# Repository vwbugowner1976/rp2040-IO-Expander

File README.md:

# RP2040-Zero BLE I/O Rev.W

Fresh mechanical-master revision for the RP2040-Zero BLE adapter concept.

- 18 × 23.5 mm
- RP2040-Zero THT/castellation geometry from the supplied master footprint
- USB-C + BOOT + RESET on F.Cu side
- 24P FFC on B.Cu side
- MDBT50Q-1MV2 is a separate core board
- FFC 1–20 = GPIO0–15, GPIO26–29
- FFC 21 = 3V3
- FFC 22 = GND
- FFC 23 = VSYS
- FFC 24 = USB_VBUS

This is the clean mechanical/electrical-interface baseline. PCB routing is intentionally kept separate from the mechanical master so it does not silently corrupt the reference geometry.

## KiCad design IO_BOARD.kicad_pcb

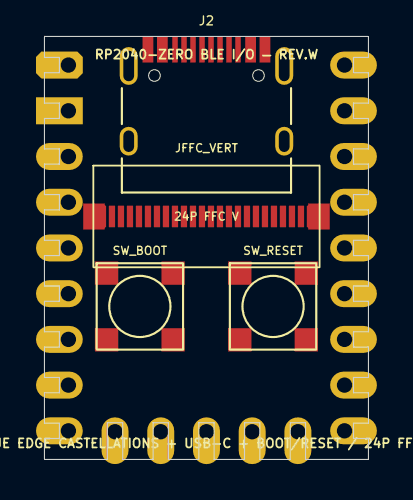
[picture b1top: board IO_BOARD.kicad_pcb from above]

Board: 4 copper layers, 18.0 x 23.5 mm, 6 parts (1 on the bottom side), 28 nets, no tracks yet.

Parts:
J2: TYPE-C-31-M-12
JFFC: FH34SRJ-24S-0.5SH(50)
JFFC_VERT: FH40-24S-0.5SV
JLEG: RP2040-Zero-THT; RP2040-Zero-THT-Castellation-Master
SW_BOOT: TS-1187A-B-A-B / C318884; SW-SMD_4P-L5.1-W5.1-P3.70-LS6.5-TL_H1.5
SW_RESET: TS-1187A-B-A-B / C318884; SW-SMD_4P-L5.1-W5.1-P3.70-LS6.5-TL_H1.5

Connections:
3V3: JFFC.21, JFFC_VERT.21, JLEG.30
BOOT: SW_BOOT.2, SW_BOOT.3
GND: J2.A1, J2.A12, J2.B1, J2.B12, JFFC.22, JFFC_VERT.22, JLEG.31, SW_BOOT.1, SW_BOOT.4, SW_RESET.1, SW_RESET.4
GPIO0: JFFC.1, JFFC_VERT.1, JLEG.0
GPIO1: JFFC.2, JFFC_VERT.2, JLEG.1
GPIO2: JFFC.3, JFFC_VERT.3, JLEG.2
GPIO3: JFFC.4, JFFC_VERT.4, JLEG.3
GPIO4: JFFC.5, JFFC_VERT.5, JLEG.4
GPIO5: JFFC.6, JFFC_VERT.6, JLEG.5
GPIO6: JFFC.7, JFFC_VERT.7, JLEG.6
GPIO7: JFFC.8, JFFC_VERT.8, JLEG.7
GPIO8: JFFC.9, JFFC_VERT.9, JLEG.8
GPIO9: JFFC.10, JFFC_VERT.10, JLEG.9
GPIO10: JFFC.11, JFFC_VERT.11, JLEG.10
GPIO11: JFFC.12, JFFC_VERT.12, JLEG.11
GPIO12: JFFC.13, JFFC_VERT.13, JLEG.12
GPIO13: JFFC.14, JFFC_VERT.14, JLEG.13
GPIO14: JFFC.15, JFFC_VERT.15, JLEG.14
GPIO15: JFFC.16, JFFC_VERT.16, JLEG.15
GPIO26: JFFC.17, JFFC_VERT.17, JLEG.26
GPIO27: JFFC.18, JFFC_VERT.18, JLEG.27
GPIO28: JFFC.19, JFFC_VERT.19, JLEG.28
GPIO29: JFFC.20, JFFC_VERT.20, JLEG.29
RESET: SW_RESET.2, SW_RESET.3
USB_D+: J2.A6, J2.B6
USB_D-: J2.A7, J2.B7
USB_VBUS: J2.A4, J2.A9, J2.B4, J2.B9, JFFC.24, JFFC_VERT.24
VSYS: JFFC.23, JFFC_VERT.23, JLEG.32

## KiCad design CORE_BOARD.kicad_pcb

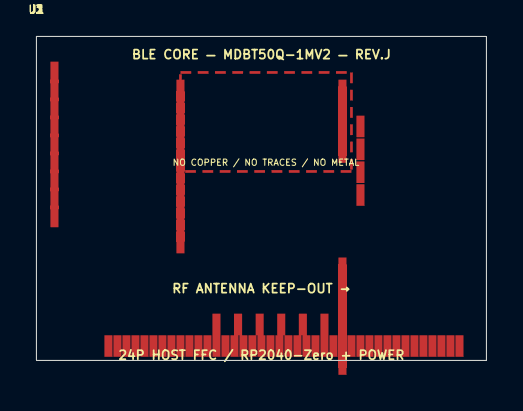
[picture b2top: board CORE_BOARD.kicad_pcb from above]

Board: 4 copper layers, 25.0 x 18.0 mm, 4 parts (0 on the bottom side), 24 nets, no tracks yet.

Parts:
J1: FH34SRJ-24S-0.5SH(50)
J2: SWD-4P
J3: CORE-EXPANSION
U1: MDBT50Q-1MV2

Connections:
3V3: J1.21, J2.1
GND: J1.22, J1.37, J1.38, J1.39, J1.40, J2.4, U1.1, U1.2, U1.15, U1.55
GPIO0: J1.1, U1.9
GPIO1: J1.2, U1.20
GPIO2: J1.3, U1.21
GPIO3: J1.4, U1.22
GPIO4: J1.5, U1.23
GPIO5: J1.6, U1.24
GPIO14: J1.15, U1.41
GPIO15: J1.16, U1.42
GPIO26: J1.17, U1.44
GPIO27: J1.18, U1.43
GPIO28: J1.19, U1.46
GPIO29: J1.20, U1.45
NC: U1.3, U1.4, U1.5, U1.6, U1.7, U1.8, U1.10, U1.11, U1.12, U1.13, U1.14, U1.17, U1.18, U1.19, U1.47, U1.48, U1.49, U1.50, U1.52, U1.54
STATUS_LED: J1.28, U1.16
SWDCLK: J1.30, J2.3, U1.53
SWDIO: J1.29, J2.2, U1.51
TB1: J1.31, U1.56
TB2: J1.32, U1.57
TB3: J1.33, U1.58
TB4: J1.34, U1.59
TB5: J1.35, U1.60
TB6: J1.36, U1.61
